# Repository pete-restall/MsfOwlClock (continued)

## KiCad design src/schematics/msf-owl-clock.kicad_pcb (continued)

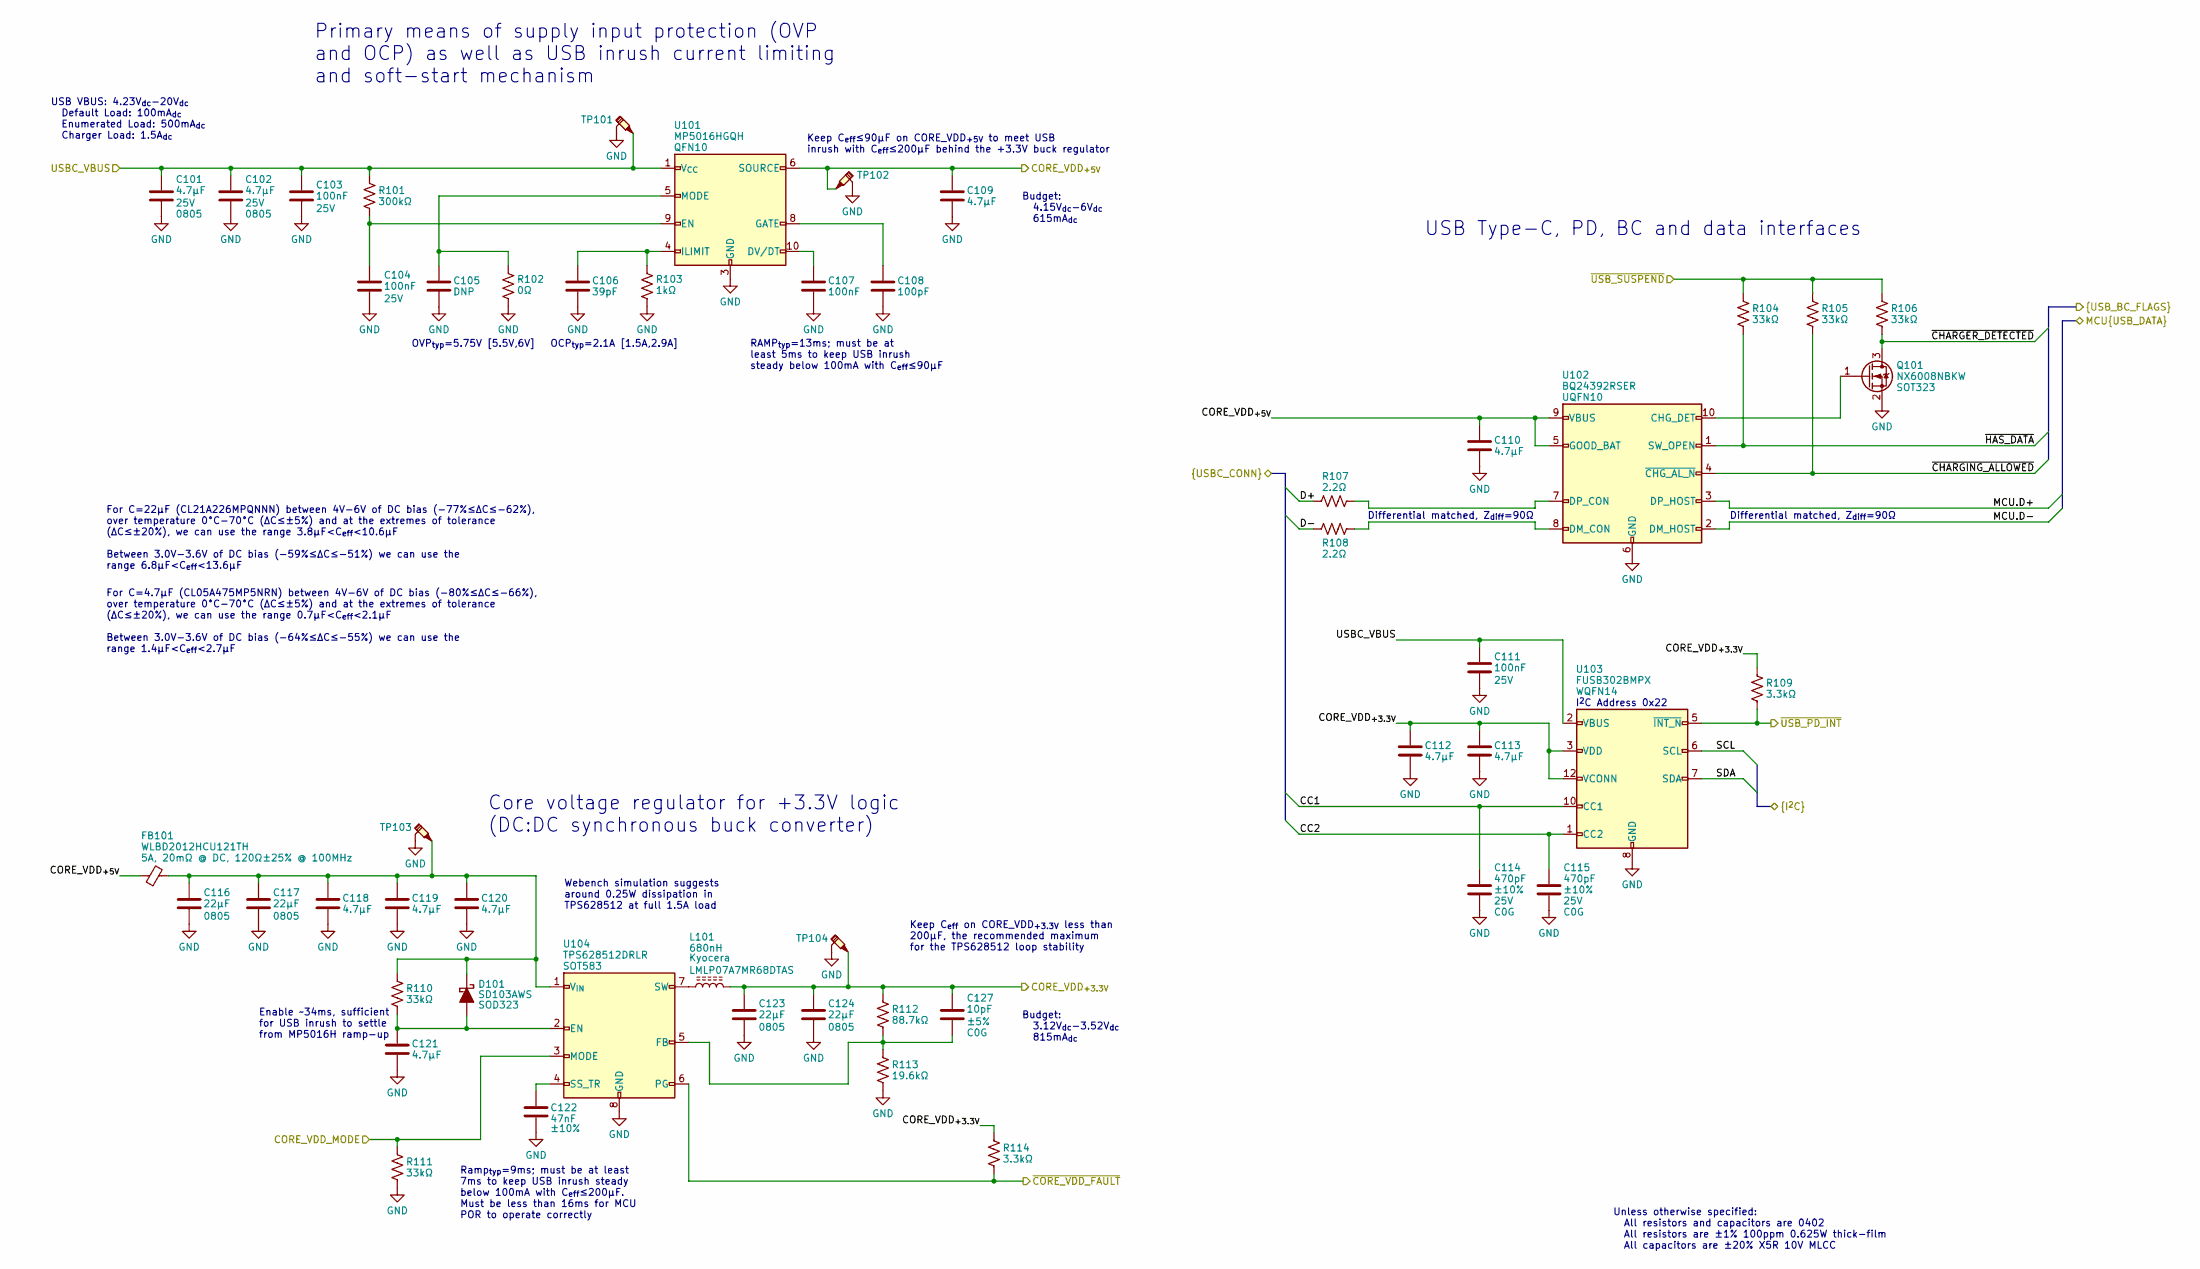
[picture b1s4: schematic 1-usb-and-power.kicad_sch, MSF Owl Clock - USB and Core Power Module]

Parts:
C101, C102: 4.7μF; unpolarised-nominal-0805-2012; Tolerance ±10%; VoltageRating 25V; ManufacturerPartNumber CL21A475KAQNNNE
C103, C104, C111: 100nF; unpolarised-nominal-0402-1005; Tolerance ±20%; VoltageRating 25V; ManufacturerPartNumber CL05B104KA5NNNC
C105: DNP; unpolarised-nominal-0402-1005; Tolerance ±10%; VoltageRating 10V
C106: 39pF; unpolarised-nominal-0402-1005; Tolerance ±10%; VoltageRating 10V; ManufacturerPartNumber CC0402JRNPO9BN390
C107: 100nF; unpolarised-nominal-0402-1005; Tolerance ±20%; VoltageRating 10V; ManufacturerPartNumber CL05B104KA5NNNC
C108: 100pF; unpolarised-nominal-0402-1005; Tolerance ±10%; VoltageRating 10V; ManufacturerPartNumber GMC04CG101G50NT
C109, C110, C112, C113, C118, C119, C120, C121: 4.7μF; unpolarised-nominal-0402-1005; Tolerance ±20%; VoltageRating 10V; ManufacturerPartNumber CL05A475MP5NRNC
C114, C115: 470pF; unpolarised-nominal-0402-1005; Tolerance ±10%; VoltageRating 25V; ManufacturerPartNumber GCM1555C1H471FA16D
C116, C117, C123, C124: 22μF; unpolarised-nominal-0805-2012; Tolerance ±20%; VoltageRating 10V; ManufacturerPartNumber CL21A226MPQNNN
C122: 47nF; unpolarised-nominal-0402-1005; Tolerance ±10%; VoltageRating 10V; ManufacturerPartNumber VJ0402Y473KXQCW1BC
C127: 10pF; unpolarised-nominal-0402-1005; Tolerance ±5%; VoltageRating 10V; ManufacturerPartNumber 885012005007
D101: SD103AWS; SOD323; ManufacturerPartNumber SD103AWS
FB101: WLBD2012HCU121TH; WLBD2012; Tolerance ±25%; ManufacturerPartNumber WLBD2012HCU121TH
L101: 680nH; 07A7; Tolerance ±20%; ManufacturerPartNumber LMLP07A7MR68DTAS
Q101: NX6008NBKW; SOT323; ManufacturerPartNumber NX6008NBKW
R101: 300kΩ; nominal-0402-1005; Tolerance ±1%; ManufacturerPartNumber RC0402FR-07300KL
R102: 0Ω; nominal-0402-1005; Tolerance ±1%; ManufacturerPartNumber RC0402FR-070RL
R103: 1kΩ; nominal-0402-1005; Tolerance ±1%; ManufacturerPartNumber WR04X1001FTL
R104, R105, R106, R110, R111: 33kΩ; nominal-0402-1005; Tolerance ±1%; ManufacturerPartNumber WR04X3302FTL
R107, R108: 2.2Ω; nominal-0402-1005; Tolerance ±1%; ManufacturerPartNumber RMCF0402FT2R20
R109, R114: 3.3kΩ; nominal-0402-1005; Tolerance ±1%; ManufacturerPartNumber CRCW04022R20FKED
R112: 88.7kΩ; nominal-0402-1005; Tolerance ±1%; ManufacturerPartNumber WR04X8872FTL
R113: 19.6kΩ; nominal-0402-1005; Tolerance ±1%; ManufacturerPartNumber WR04X1962FTL
TP101, TP102, TP103, TP104: testpoint-SP3050A-with-short-gnd
U101: MP5016HGQH; QFN10-1.5x2.0mm-0.5mm; ManufacturerPartNumber MP5016HGQH
U102: BQ24392RSER; UQFN10-1.5x2.0mm-0.5mm; ManufacturerPartNumber BQ24392RSER
U103: FUSB302BMPX; WQFN14-2.5x2.5mm-0.5mm-expad-1.45x1.45mm-thermvias; ManufacturerPartNumber FUSB302BMPX
U104: TPS628512DRLR; SOT583; ManufacturerPartNumber TPS628512DRLR

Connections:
/1-usb-and-power/CC1: C114.1, U103.10 (CC1), U103.11 (CC1); also elsewhere on the board
/1-usb-and-power/CC2: C115.1, U103.1 (CC2), U103.14 (CC2); also elsewhere on the board
/1-usb-and-power/CORE_VDD_MODE: R111.1, U104.3 (MODE); also elsewhere on the board
/1-usb-and-power/CORE_VDD_{+5V}: C109.1, C110.1, FB101.1 (P1_PWRIN), TP102.1, U101.6 (SOURCE), U102.5 (GOOD_BAT), U102.9 (VBUS); also elsewhere on the board
/1-usb-and-power/D+: R107.1; also elsewhere on the board
/1-usb-and-power/D-: R108.1; also elsewhere on the board
/1-usb-and-power/MCU.D+: U102.3 (DP_HOST); also elsewhere on the board
/1-usb-and-power/MCU.D-: U102.2 (DM_HOST); also elsewhere on the board
/1-usb-and-power/SCL: U103.6 (SCL); also elsewhere on the board
/1-usb-and-power/SDA: U103.7 (SDA); also elsewhere on the board
/1-usb-and-power/USBC_VBUS: C101.1, C102.1, C103.1, C111.1, R101.1, TP101.1, U101.1 (V_{CC}), U103.2 (VBUS); also elsewhere on the board
/1-usb-and-power/~CHARGER_DETECTED: Q101.3 (D), R106.2; also elsewhere on the board
/1-usb-and-power/~CHARGING_ALLOWED: R105.2, U102.4 (~CHG_AL_N); also elsewhere on the board
/1-usb-and-power/~CORE_VDD_FAULT: R114.2, U104.6 (PG); also elsewhere on the board
/1-usb-and-power/~HAS_DATA: R104.2, U102.1 (SW_OPEN); also elsewhere on the board
/1-usb-and-power/~USB_PD_INT: R109.2, U103.5 (~INT_N); also elsewhere on the board
/1-usb-and-power/~USB_SUSPEND: R104.1, R105.1, R106.1; also elsewhere on the board
/CORE_VDD_{+3.3V}: C112.1, C113.1, C123.1, C124.1, C127.1, L101.2 (P2_PWROUT), R109.1, R112.1, R114.1, TP104.1, U103.3 (VDD), U103.4 (VDD), U103.12 (VCONN), U103.13 (VCONN); also elsewhere on the board
unnamed: C121.1, D101.2 (A), R110.2, U104.2 (EN)
unnamed: C116.1, C117.1, C118.1, C119.1, C120.1, D101.1 (K), FB101.2 (P2_PWROUT), R110.1, TP103.1, U104.1 (V_{IN})
unnamed: L101.1, U104.7 (SW)
unnamed: Q101.1 (G), U102.10 (CHG_DET)
unnamed: C107.1, U101.10 (DV/DT)
unnamed: C104.1, R101.2, U101.9 (EN)
unnamed: C108.1, U101.8 (GATE)
unnamed: C106.1, R103.1, U101.4 (ILIMIT)
unnamed: C105.1, R102.1, U101.5 (MODE)
unnamed: R108.2, U102.8 (DM_CON)
unnamed: R107.2, U102.7 (DP_CON)
unnamed: C127.2, R112.2, R113.1, U104.5 (FB)
unnamed: C122.1, U104.4 (SS_TR)

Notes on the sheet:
Unless otherwise specified: All resistors and capacitors are 0402 All resistors are ±1% 100ppm 0.625W thick-film All capacitors are ±20% X5R 10V MLCC
Ramp_{typ}=9ms; must be at least 7ms to keep USB inrush steady below 100mA with C_{eff}≤200μF. Must be less than 16ms for MCU POR to operate correctly
Webench simulation suggests around 0.25W dissipation in TPS628512 at full 1.5A load
I^{2}C Address 0x22
Keep C_{eff}≤90μF on CORE_VDD_{+5V} to meet USB inrush with C_{eff}≤200μF behind the +3.3V buck regulator
Differential matched, Z_{diff}=90Ω
Enable ~34ms, sufficient for USB inrush to settle from MP5016H ramp-up
Primary means of supply input protection (OVP and OCP) as well as USB inrush current limiting and soft-start mechanism
Budget: 4.15V_{dc}-6V_{dc} 615mA_{dc}
For C=22μF (CL21A226MPQNNN) between 4V-6V of DC bias (-77%≤ΔC≤-62%), over temperature 0°C-70°C (ΔC≤±5%) and at the extremes of tolerance (ΔC≤±20%), we can use the range 3.8μF<C_{eff}<10.6μF Between 3.0V-3.6V of DC bias (-59%≤ΔC≤-51%) we can use the range 6.8μF<C_{eff}<13.6μF
Budget: 3.12V_{dc}-3.52V_{dc} 815mA_{dc}
USB VBUS: 4.23V_{dc}-20V_{dc} Default Load: 100mA_{dc} Enumerated Load: 500mA_{dc} Charger Load: 1.5A_{dc}
RAMP_{typ}=13ms; must be at least 5ms to keep USB inrush steady below 100mA with C_{eff}≤90μF
OCP_{typ}=2.1A [1.5A,2.9A]
Core voltage regulator for +3.3V logic (DC:DC synchronous buck converter)
For C=4.7μF (CL05A475MP5NRN) between 4V-6V of DC bias (-80%≤ΔC≤-66%), over temperature 0°C-70°C (ΔC≤±5%) and at the extremes of tolerance (ΔC≤±20%), we can use the range 0.7μF<C_{eff}<2.1μF Between 3.0V-3.6V of DC bias (-64%≤ΔC≤-55%) we can use the range 1.4μF<C_{eff}<2.7μF
OVP_{typ}=5.75V [5.5V,6V]
Keep C_{eff} on CORE_VDD_{+3.3V} less than 200μF, the recommended maximum for the TPS628512 loop stability
USB Type-C, PD, BC and data interfaces

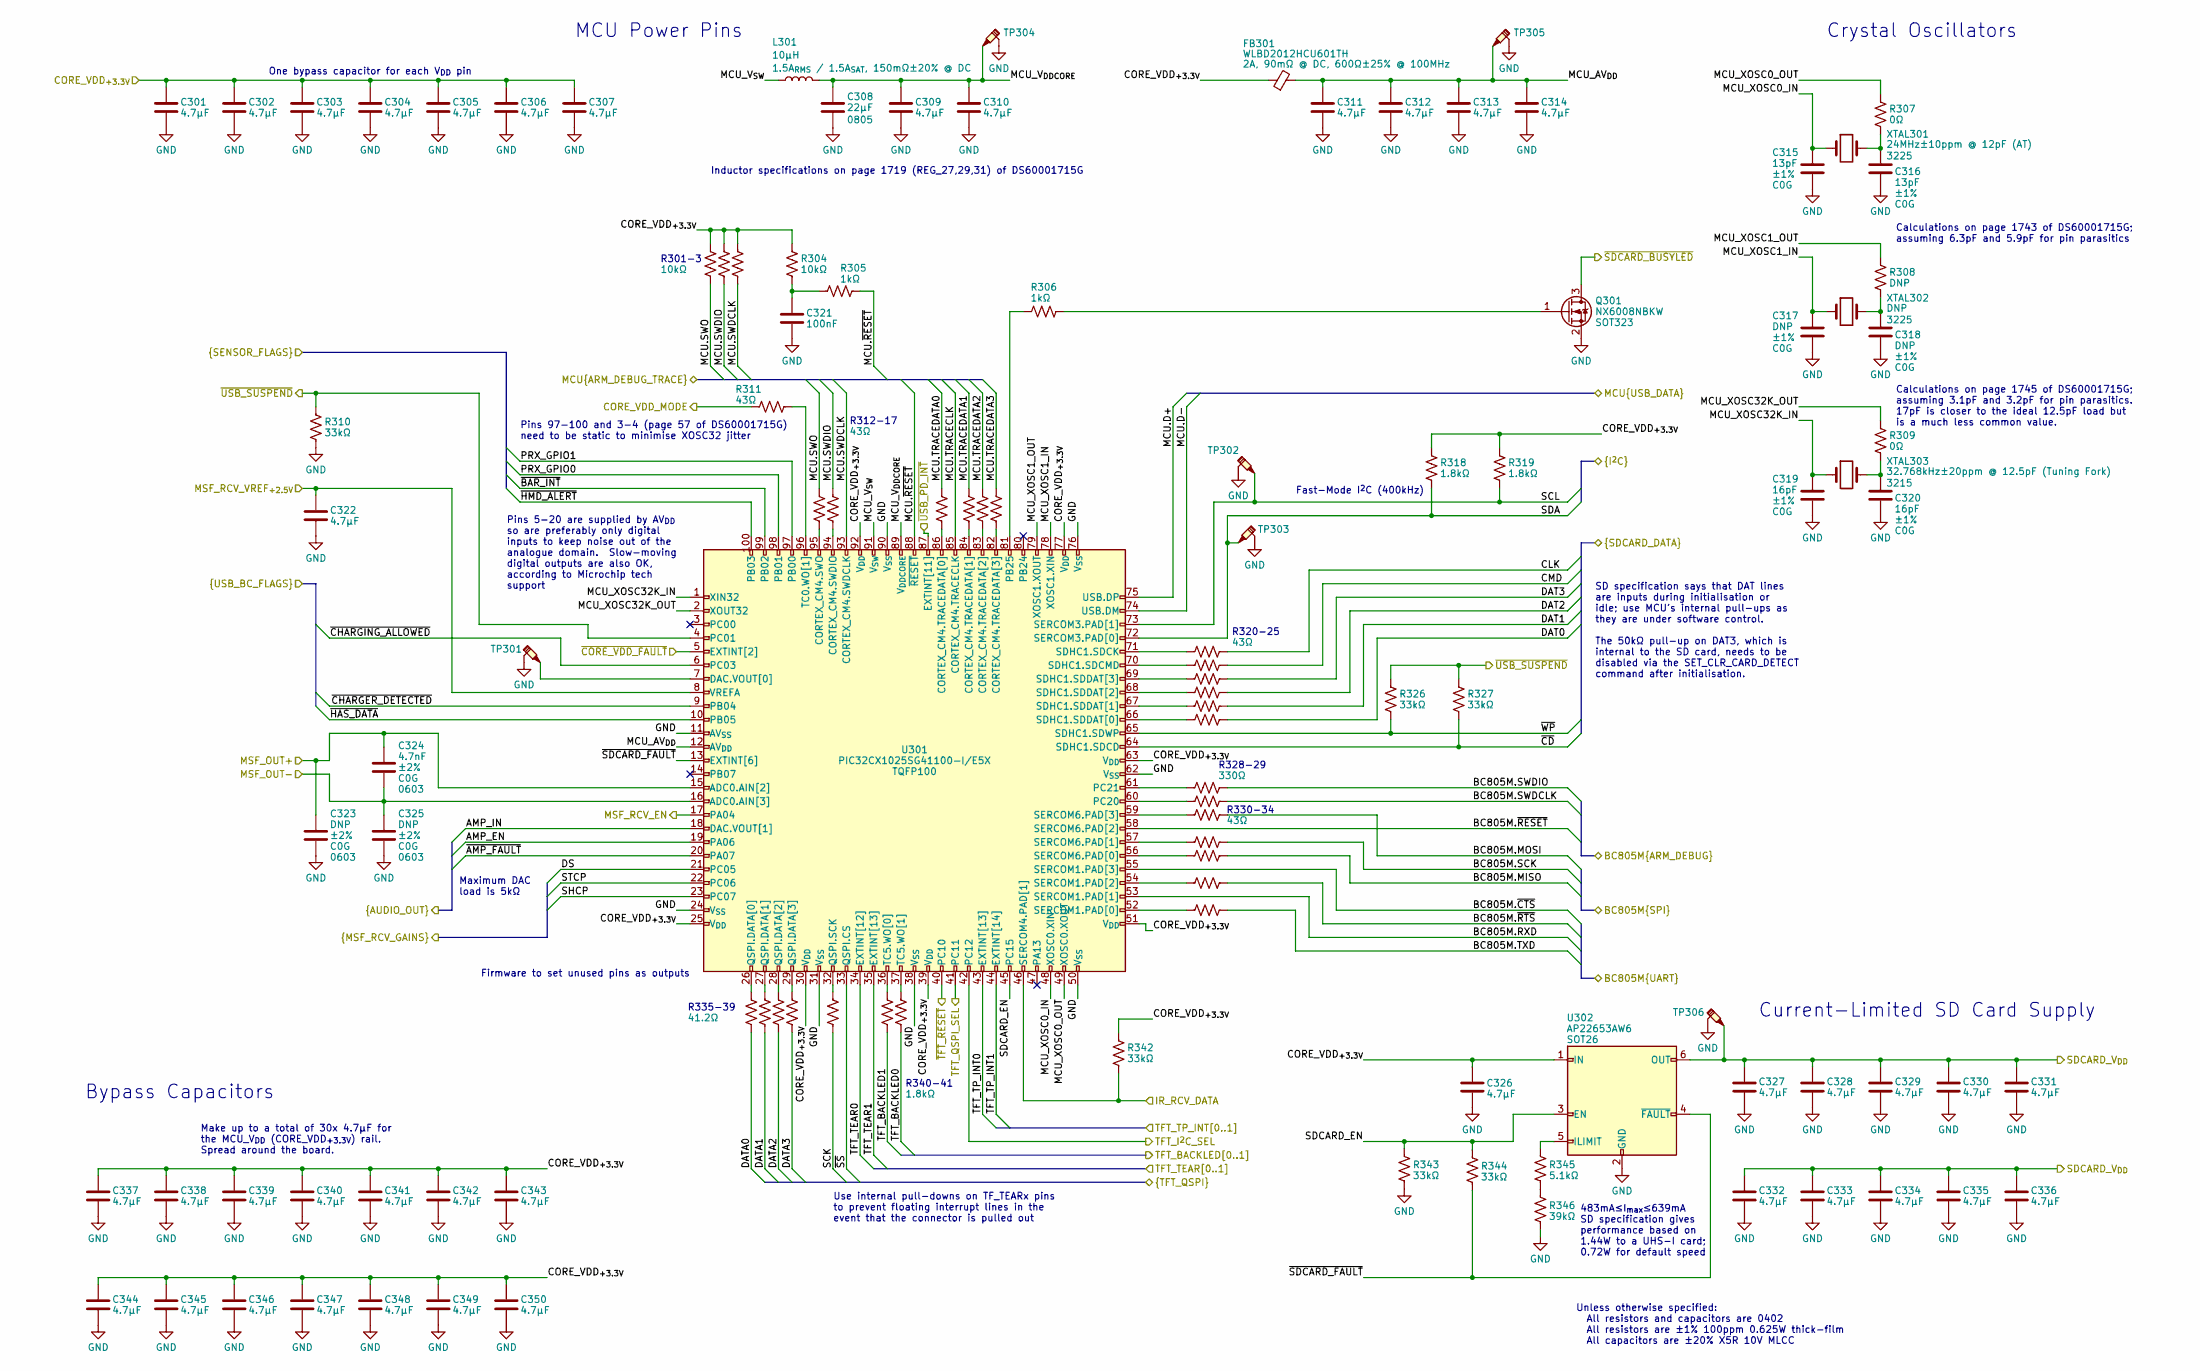
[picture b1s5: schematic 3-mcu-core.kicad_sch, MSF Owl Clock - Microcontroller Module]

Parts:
C301, C302, C303, C304, C305, C306, C307, C309, C310, C311, C312, C313, C314, C322, C326, C327, C328, C329, C330, C331, C332, C333, C334, C335, C336, C337, C338, C339, C340, C341, C342, C343, C344, C345, C346, C347, C348, C349, C350: 4.7μF; unpolarised-nominal-0402-1005; Tolerance ±20%; VoltageRating 10V; ManufacturerPartNumber CL05A475MP5NRNC
C308: 22μF; unpolarised-nominal-0805-2012; Tolerance ±20%; VoltageRating 10V; ManufacturerPartNumber CL21A226MPQNNN
C315, C316: 13pF; unpolarised-nominal-0402-1005; Tolerance ±1%; VoltageRating 10V; ManufacturerPartNumber GJM1555C1H130FB01D
C317, C318: DNP; unpolarised-nominal-0402-1005; Tolerance ±1%; VoltageRating 10V
C319, C320: 16pF; unpolarised-nominal-0402-1005; Tolerance ±1%; VoltageRating 10V; ManufacturerPartNumber GCM1555C1H160FA16D
C321: 100nF; unpolarised-nominal-0402-1005; Tolerance ±20%; VoltageRating 10V; ManufacturerPartNumber CL05B104KA5NNNC
C323, C325: DNP; unpolarised-nominal-0603-1608; Tolerance ±2%; VoltageRating 10V
C324: 4.7nF; unpolarised-nominal-0603-1608; Tolerance ±2%; VoltageRating 10V; ManufacturerPartNumber CC0603FRNPO9BN472
FB301: WLBD2012HCU601TH; WLBD2012; Tolerance ±25%; ManufacturerPartNumber WLBD2012HCU601TH
L301: 10μH; HPC4018NF; Tolerance ±20%; ManufacturerPartNumber HPC4018NF-100M
Q301: NX6008NBKW; SOT323; ManufacturerPartNumber NX6008NBKW
R301, R302, R303, R304: 10kΩ; nominal-0402-1005; Tolerance ±1%; ManufacturerPartNumber WR04X1002FTL
R305, R306: 1kΩ; nominal-0402-1005; Tolerance ±1%; ManufacturerPartNumber WR04X1001FTL
R307, R309: 0Ω; nominal-0402-1005; Tolerance ±1%; ManufacturerPartNumber RC0402FR-070RL
R308: DNP; nominal-0402-1005; Tolerance ±1%
R310, R326, R327, R342, R343, R344: 33kΩ; nominal-0402-1005; Tolerance ±1%; ManufacturerPartNumber WR04X3302FTL
R311, R312, R313, R314, R315, R316, R317, R320, R321, R322, R323, R324, R325, R330, R331, R332, R333, R334: 43Ω; nominal-0402-1005; Tolerance ±1%; ManufacturerPartNumber RC0402FR-0743RL
R318, R319, R340, R341: 1.8kΩ; nominal-0402-1005; Tolerance ±1%; ManufacturerPartNumber RC0402FR-071K8L
R328, R329: 330Ω; nominal-0402-1005; Tolerance ±1%; ManufacturerPartNumber WR04X3300FTL
R335, R336, R337, R338, R339: 41.2Ω; nominal-0402-1005; Tolerance ±1%; ManufacturerPartNumber RC0402FR-0741R2L
R345: 5.1kΩ; nominal-0402-1005; Tolerance ±1%; ManufacturerPartNumber WR04X5101FTL
R346: 39kΩ; nominal-0402-1005; Tolerance ±1%; ManufacturerPartNumber RC0402FR-0739KL
TP301, TP302, TP303, TP304, TP305, TP306: testpoint-SP3050A-with-short-gnd
U301: PIC32CX1025SG41100-I/E5X; TQFP100-14x14mm-0.5mm; ManufacturerPartNumber PIC32CX1025SG41100-I/E5X
U302: AP22653AW6; SOT26; ManufacturerPartNumber AP22653AW6-7
XTAL301: 24MHz; 3225-1-3; Tolerance ±10ppm; ManufacturerPartNumber RH100-24.000-12-1010-EXT-TR
XTAL302: 8-48MHz; 3225-1-3; Tolerance ±10ppm
XTAL303: 32.768kHz; 3215; Tolerance ±20ppm; ManufacturerPartNumber DH2032K768C5T1521011

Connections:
/1-usb-and-power/CORE_VDD_MODE: R311.1; also elsewhere on the board
/1-usb-and-power/MCU.D+: U301.75 (USB.DP); also elsewhere on the board
/1-usb-and-power/MCU.D-: U301.74 (USB.DM); also elsewhere on the board
/1-usb-and-power/SCL: R319.2, TP302.1, U301.73 (SERCOM3.PAD[1]); also elsewhere on the board
/1-usb-and-power/SDA: R318.2, TP303.1, U301.72 (SERCOM3.PAD[0]); also elsewhere on the board
/1-usb-and-power/~CHARGER_DETECTED: U301.9 (PB04); also elsewhere on the board
/1-usb-and-power/~CHARGING_ALLOWED: U301.6 (PC03); also elsewhere on the board
/1-usb-and-power/~CORE_VDD_FAULT: U301.5 (EXTINT[2]); also elsewhere on the board
/1-usb-and-power/~HAS_DATA: U301.10 (PB05); also elsewhere on the board
/1-usb-and-power/~USB_PD_INT: U301.87 (EXTINT[11]); also elsewhere on the board
/1-usb-and-power/~USB_SUSPEND: R310.1, R326.1, R327.1, U301.4 (PC01); also elsewhere on the board
/2-msf-receiver/DS: U301.21 (PC05); also elsewhere on the board
/2-msf-receiver/MSF_OUT+: C323.2, C324.2, U301.15 (ADC0.AIN[2]); also elsewhere on the board
/2-msf-receiver/MSF_OUT-: C324.1, C325.2, U301.16 (ADC0.AIN[3]); also elsewhere on the board
/2-msf-receiver/MSF_RCV_EN: U301.17 (PA04); also elsewhere on the board
/2-msf-receiver/MSF_RCV_VREF_{+2.5V}: C322.1, U301.8 (VREFA); also elsewhere on the board
/2-msf-receiver/SHCP: U301.23 (PC07); also elsewhere on the board
/2-msf-receiver/STCP: U301.22 (PC06); also elsewhere on the board
/3-mcu-core/AMP_EN: U301.19 (PA06); also elsewhere on the board
/3-mcu-core/AMP_IN: U301.18 (DAC.VOUT[1]); also elsewhere on the board
/3-mcu-core/BC805M.MISO: R332.2; also elsewhere on the board
/3-mcu-core/BC805M.MOSI: R330.2; also elsewhere on the board
/3-mcu-core/BC805M.RXD: U301.53 (SERCOM1.PAD[1]); also elsewhere on the board
/3-mcu-core/BC805M.SCK: R331.2; also elsewhere on the board
/3-mcu-core/BC805M.SWDCLK: R329.2; also elsewhere on the board
/3-mcu-core/BC805M.SWDIO: R328.2; also elsewhere on the board
/3-mcu-core/BC805M.TXD: R334.2; also elsewhere on the board
/3-mcu-core/BC805M.~CTS: U301.55 (SERCOM1.PAD[3]); also elsewhere on the board
/3-mcu-core/BC805M.~RESET: U301.58 (SERCOM6.PAD[2]); also elsewhere on the board
/3-mcu-core/BC805M.~RTS: R333.2; also elsewhere on the board
/3-mcu-core/CLK: R320.2; also elsewhere on the board
/3-mcu-core/CMD: R321.2; also elsewhere on the board
/3-mcu-core/DAT0: R325.2; also elsewhere on the board
/3-mcu-core/DAT1: R324.2; also elsewhere on the board
/3-mcu-core/DAT2: R323.2; also elsewhere on the board
/3-mcu-core/DAT3: R322.2; also elsewhere on the board
/3-mcu-core/DATA0: R335.1; also elsewhere on the board
/3-mcu-core/DATA1: R336.1; also elsewhere on the board
/3-mcu-core/DATA2: R337.1; also elsewhere on the board
/3-mcu-core/DATA3: R338.1; also elsewhere on the board
/3-mcu-core/IR_RCV_DATA: R342.2, U301.46 (SERCOM4.PAD[1]); also elsewhere on the board
/3-mcu-core/MCU.SWDCLK: R303.1, U301.93 (CORTEX_CM4.SWDCLK); also elsewhere on the board
/3-mcu-core/MCU.SWDIO: R302.1, R313.2; also elsewhere on the board
/3-mcu-core/MCU.SWO: R301.1, R312.2; also elsewhere on the board
/3-mcu-core/MCU.TRACECLK: U301.85 (CORTEX_CM4.TRACECLK); also elsewhere on the board
/3-mcu-core/MCU.TRACEDATA0: R314.2; also elsewhere on the board
/3-mcu-core/MCU.TRACEDATA1: R315.2; also elsewhere on the board
/3-mcu-core/MCU.TRACEDATA2: R316.2; also elsewhere on the board
/3-mcu-core/MCU.TRACEDATA3: R317.2; also elsewhere on the board
/3-mcu-core/MCU.~RESET: R305.2, U301.88 (~RESET); also elsewhere on the board
/3-mcu-core/MCU_AV_{DD}: C311.1, C312.1, C313.1, C314.1, FB301.2 (P2_PWROUT), TP305.1, U301.12 (AV_{DD})
/3-mcu-core/MCU_V_{DDCORE}: C308.1, C309.1, C310.1, L301.2, TP304.1, U301.89 (V_{DDCORE})
/3-mcu-core/MCU_V_{SW}: L301.1, U301.91 (V_{SW})
/3-mcu-core/MCU_XOSC0_IN: C315.1, U301.48 (XOSC0.XIN), XTAL301.1
/3-mcu-core/MCU_XOSC0_OUT: R307.1, U301.49 (XOSC0.XOUT)
/3-mcu-core/MCU_XOSC1_IN: C317.1, U301.78 (XOSC1.XIN), XTAL302.1
/3-mcu-core/MCU_XOSC1_OUT: R308.1, U301.79 (XOSC1.XOUT)
/3-mcu-core/MCU_XOSC32K_IN: C319.1, U301.1 (XIN32), XTAL303.1
/3-mcu-core/MCU_XOSC32K_OUT: R309.1, U301.2 (XOUT32)
/3-mcu-core/PRX_GPIO0: U301.98 (PB01); also elsewhere on the board
/3-mcu-core/PRX_GPIO1: U301.97 (PB00); also elsewhere on the board
/3-mcu-core/SCK: R339.1; also elsewhere on the board
/3-mcu-core/SDCARD_EN: R343.1, R344.1, U301.45 (PC15), U302.3 (EN)
/3-mcu-core/SDCARD_V_{DD}: C327.1, C328.1, C329.1, C330.1, C331.1, C332.1, C333.1, C334.1, C335.1, C336.1, TP306.1, U302.6 (OUT); also elsewhere on the board
/3-mcu-core/TFT_BACKLED0: R341.1; also elsewhere on the board
/3-mcu-core/TFT_BACKLED1: R340.1; also elsewhere on the board
/3-mcu-core/TFT_I^{2}C_SEL: U301.42 (PC12); also elsewhere on the board
/3-mcu-core/TFT_QSPI_SEL: U301.41 (PC11); also elsewhere on the board
/3-mcu-core/TFT_TEAR0: U301.34 (EXTINT[12]); also elsewhere on the board
/3-mcu-core/TFT_TEAR1: U301.35 (EXTINT[13]); also elsewhere on the board
/3-mcu-core/TFT_TP_INT0: U301.43 (EXTINT[13]); also elsewhere on the board
/3-mcu-core/TFT_TP_INT1: U301.44 (EXTINT[14]); also elsewhere on the board
/3-mcu-core/~AMP_FAULT: U301.20 (PA07); also elsewhere on the board
/3-mcu-core/~BAR_INT: U301.99 (PB02); also elsewhere on the board
/3-mcu-core/~CD: R327.2, U301.64 (SDHC1.SDCD); also elsewhere on the board
/3-mcu-core/~HMD_ALERT: U301.100 (PB03); also elsewhere on the board
/3-mcu-core/~SDCARD_BUSYLED: Q301.3 (D); also elsewhere on the board
/3-mcu-core/~SDCARD_FAULT: R344.2, U301.13 (EXTINT[6]), U302.4 (~FAULT)
/3-mcu-core/~SS: U301.33 (QSPI.CS); also elsewhere on the board
/3-mcu-core/~TFT_RESET: U301.40 (PC10); also elsewhere on the board
/3-mcu-core/~WP: R326.2, U301.65 (SDHC1.SDWP); also elsewhere on the board
/CORE_VDD_{+3.3V}: C301.1, C302.1, C303.1, C304.1, C305.1, C306.1, C307.1, C326.1, C337.1, C338.1, C339.1, C340.1, C341.1, C342.1, C343.1, C344.1, C345.1, C346.1, C347.1, C348.1, C349.1, C350.1, FB301.1 (P1_PWRIN), R301.2, R302.2, R303.2, R304.1, R318.1, R319.1, R342.1, U301.25 (V_{DD}), U301.30 (V_{DD}), U301.39 (V_{DD}), U301.51 (V_{DD}), U301.63 (V_{DD}), U301.77 (V_{DD}), U301.92 (V_{DD}), U302.1 (IN); also elsewhere on the board
unnamed: C316.1, R307.2, XTAL301.3
unnamed: C318.1, R308.2, XTAL302.3
unnamed: C320.1, R309.2, XTAL303.2
unnamed: C321.1, R304.2, R305.1
unnamed: Q301.1 (G), R306.2
unnamed: R345.2, R346.1
unnamed: TP301.1, U301.7 (DAC.VOUT[0])
unnamed: R335.2, U301.26 (QSPI.DATA[0])
unnamed: R336.2, U301.27 (QSPI.DATA[1])
unnamed: R337.2, U301.28 (QSPI.DATA[2])
unnamed: R338.2, U301.29 (QSPI.DATA[3])
unnamed: R334.1, U301.52 (SERCOM1.PAD[0])
unnamed: R333.1, U301.54 (SERCOM1.PAD[2])
unnamed: R321.1, U301.70 (SDHC1.SDCMD)
unnamed: R320.1, U301.71 (SDHC1.SDCK)
unnamed: R313.1, U301.94 (CORTEX_CM4.SWDIO)
unnamed: R339.2, U301.32 (QSPI.SCK)
unnamed: R340.2, U301.36 (TC5.WO[0])
unnamed: R341.2, U301.37 (TC5.WO[1])
unnamed: R325.1, U301.66 (SDHC1.SDDAT[0])
unnamed: R324.1, U301.67 (SDHC1.SDDAT[1])
unnamed: R323.1, U301.68 (SDHC1.SDDAT[2])
unnamed: R322.1, U301.69 (SDHC1.SDDAT[3])
unnamed: R306.1, U301.81 (PB25)
unnamed: R312.1, U301.95 (CORTEX_CM4.SWO)
unnamed: R311.2, U301.96 (TC0.WO[1])
unnamed: R332.1, U301.56 (SERCOM6.PAD[0])
unnamed: R331.1, U301.57 (SERCOM6.PAD[1])
unnamed: R330.1, U301.59 (SERCOM6.PAD[3])
unnamed: R329.1, U301.60 (PC20)
unnamed: R328.1, U301.61 (PC21)
unnamed: R317.1, U301.82 (CORTEX_CM4.TRACEDATA[3])
unnamed: R316.1, U301.83 (CORTEX_CM4.TRACEDATA[2])
unnamed: R315.1, U301.84 (CORTEX_CM4.TRACEDATA[1])
unnamed: R314.1, U301.86 (CORTEX_CM4.TRACEDATA[0])
unnamed: R345.1, U302.5 (ILIMIT)

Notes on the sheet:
Fast-Mode I^{2}C (400kHz)
Current-Limited SD Card Supply
Use internal pull-downs on TF_TEARx pins to prevent floating interrupt lines in the event that the connector is pulled out
One bypass capacitor for each V_{DD} pin
Maximum DAC load is 5kΩ
R335-39
SD specification says that DAT lines are inputs during initialisation or idle; use MCU's internal pull-ups as they are under software control. The 50kΩ pull-up on DAT3, which is internal to the SD card, needs to be disabled via the SET_CLR_CARD_DETECT command after initialisation.
MCU Power Pins
Pins 5-20 are supplied by AV_{DD} so are preferably only digital inputs to keep noise out of the analogue domain. Slow-moving digital outputs are also OK, according to Microchip tech support
Pins 97-100 and 3-4 (page 57 of DS60001715G) need to be static to minimise XOSC32 jitter
Firmware to set unused pins as outputs
R330-34
R312-17
Calculations on page 1743 of DS60001715G; assuming 6.3pF and 5.9pF for pin parasitics
Make up to a total of 30x 4.7μF for the MCU_V_{DD} (CORE_VDD_{+3.3V}) rail. Spread around the board.
Unless otherwise specified: All resistors and capacitors are 0402 All resistors are ±1% 100ppm 0.625W thick-film All capacitors are ±20% X5R 10V MLCC
R340-41
Bypass Capacitors
R328-29
Calculations on page 1745 of DS60001715G; assuming 3.1pF and 3.2pF for pin parasitics. 17pF is closer to the ideal 12.5pF load but is a much less common value.
R320-25
Inductor specifications on page 1719 (REG_27,29,31) of DS60001715G
R301-3
Crystal Oscillators
483mA≤I_{max}≤639mA SD specification gives performance based on 1.44W to a UHS-I card; 0.72W for default speed

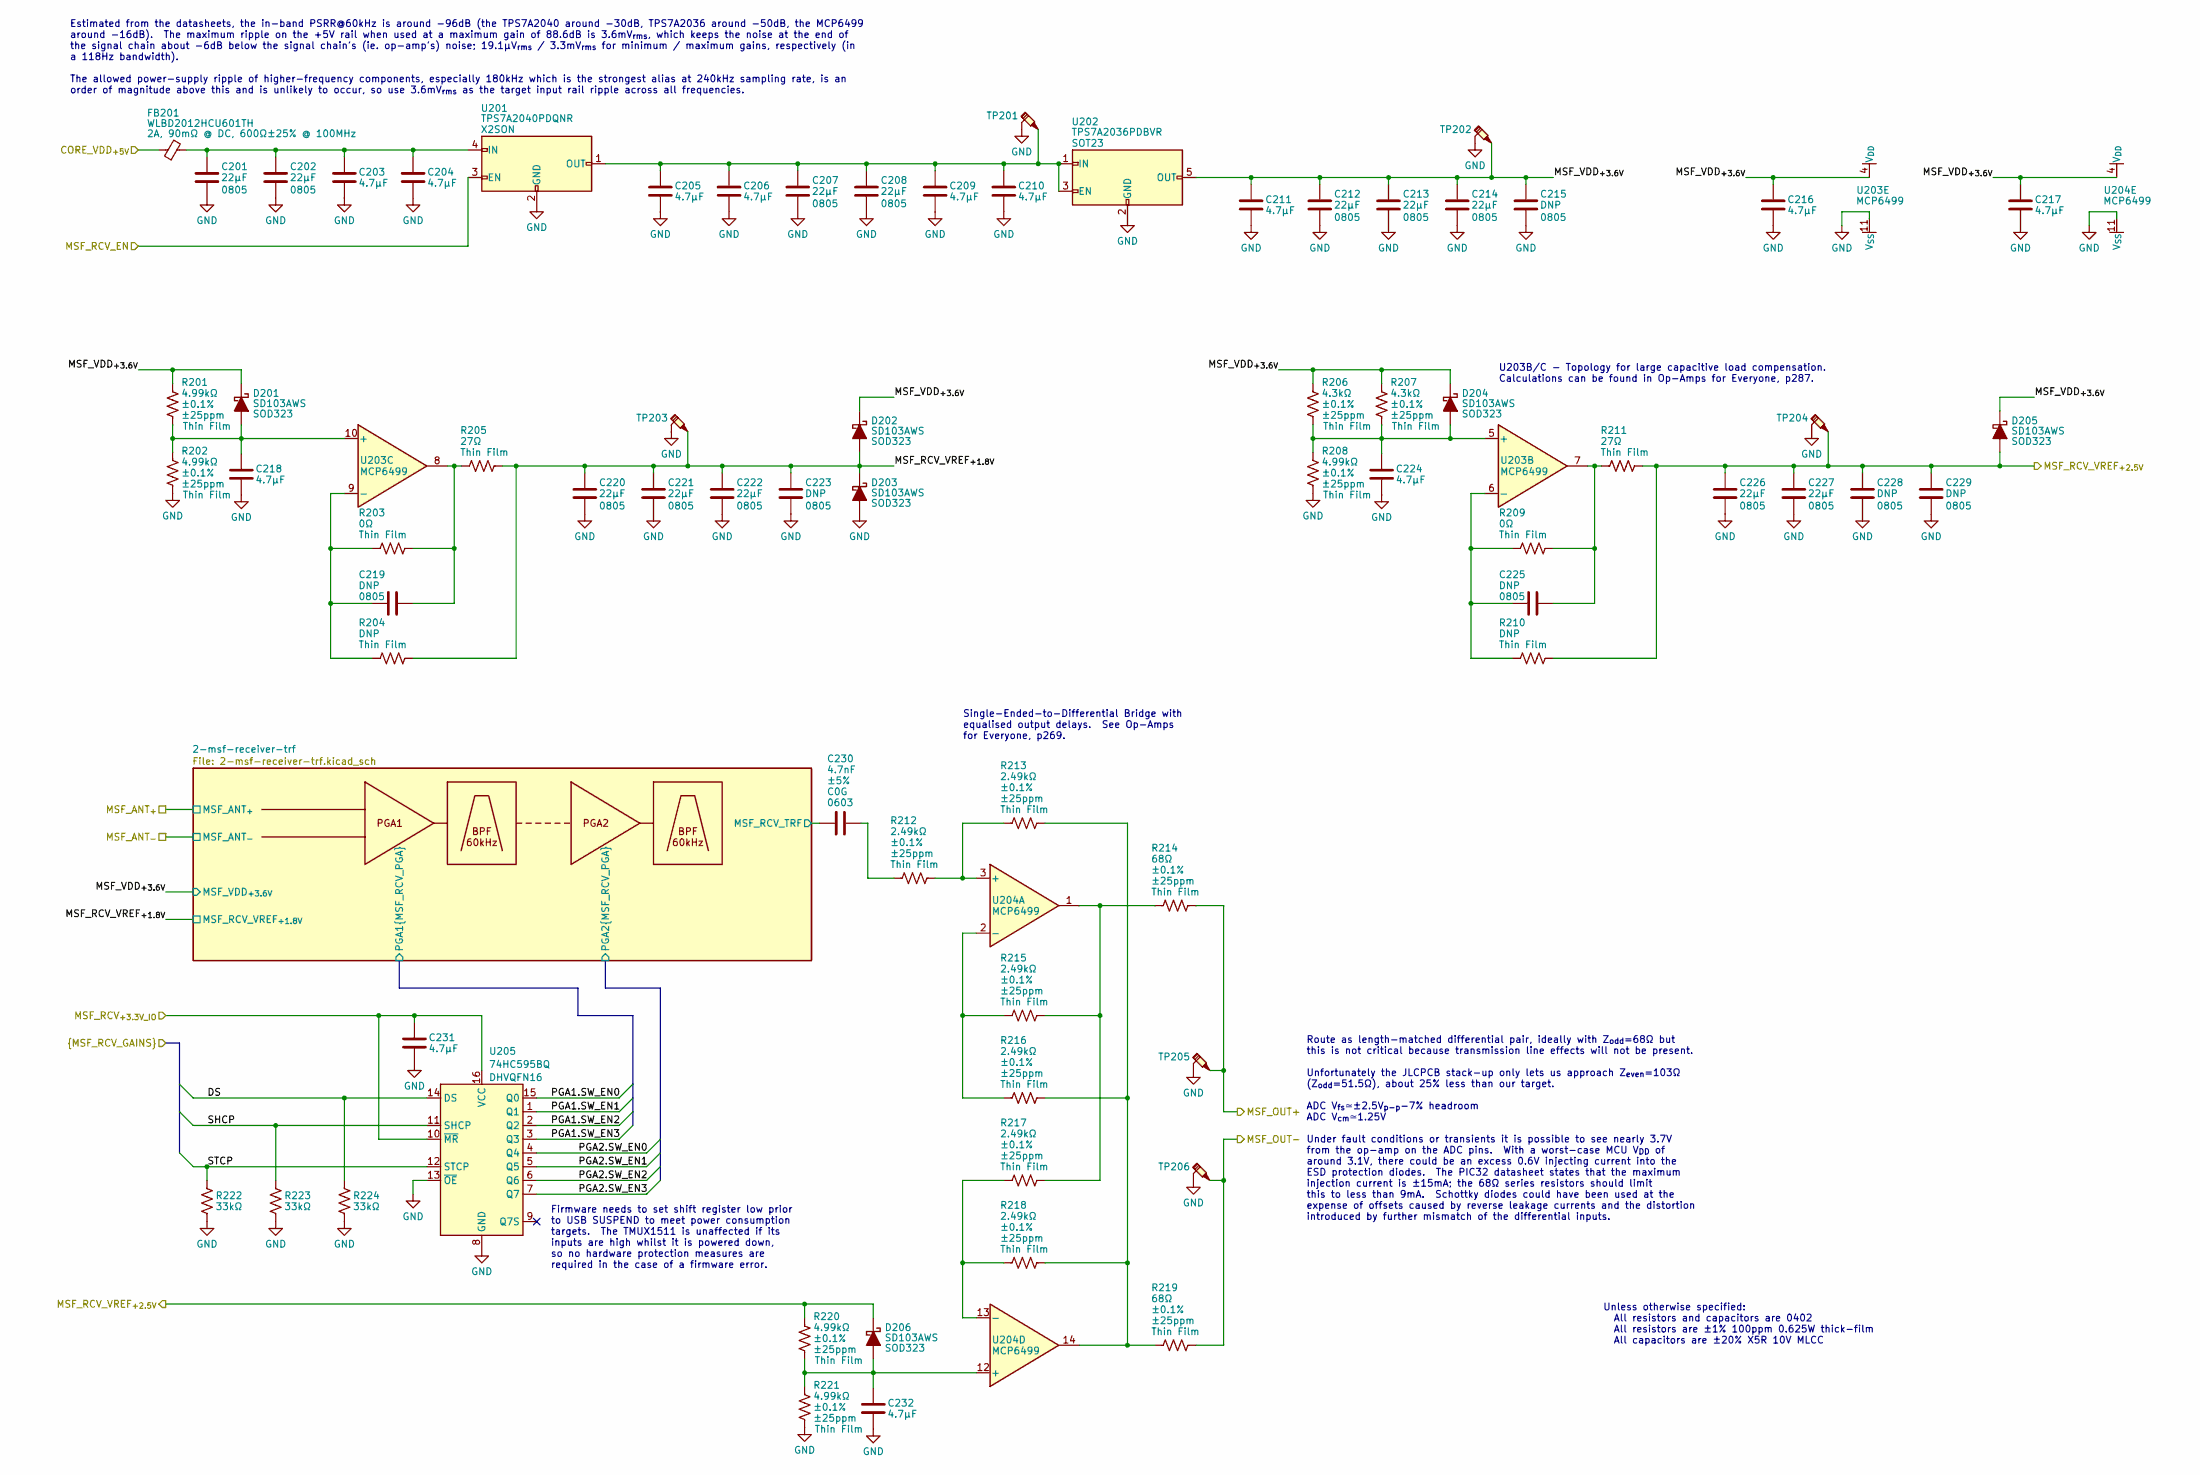
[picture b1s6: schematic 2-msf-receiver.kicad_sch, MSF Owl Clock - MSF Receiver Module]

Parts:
C201, C202, C207, C208, C212, C213, C214, C220, C221, C222, C226, C227: 22μF; unpolarised-nominal-0805-2012; Tolerance ±20%; VoltageRating 10V; ManufacturerPartNumber CL21A226MPQNNN
C203, C204, C205, C206, C209, C210, C211, C216, C217, C218, C224, C231, C232: 4.7μF; unpolarised-nominal-0402-1005; Tolerance ±20%; VoltageRating 10V; ManufacturerPartNumber CL05A475MP5NRNC
C215, C223, C228, C229: DNP; unpolarised-nominal-0805-2012; Tolerance ±20%; VoltageRating 10V; ManufacturerPartNumber CL21A226MPQNNN
C219, C225: DNP; unpolarised-nominal-0805-2012; Tolerance ±20%; VoltageRating 10V
C230: 4.7nF; unpolarised-nominal-0603-1608; Tolerance ±5%; VoltageRating 10V; ManufacturerPartNumber CC0603FRNPO9BN472
D201, D202, D203, D204, D205, D206: SD103AWS; SOD323; ManufacturerPartNumber SD103AWS
FB201: WLBD2012HCU601TH; WLBD2012; Tolerance ±25%; ManufacturerPartNumber WLBD2012HCU601TH
R201, R202, R208, R220, R221: 4.99kΩ; nominal-0402-1005; Tolerance ±0.1%; ManufacturerPartNumber RT0402BRD074K99L
R203, R209: 0Ω; nominal-0402-1005; Tolerance ±1%; ManufacturerPartNumber RC0402FR-070RL
R204, R210: DNP; nominal-0402-1005; Tolerance ±1%
R205, R211: 27Ω; nominal-0402-1005; Tolerance ±1%; ManufacturerPartNumber CPF0402B27RE1
R206, R207: 4.3kΩ; nominal-0402-1005; Tolerance ±0.1%; ManufacturerPartNumber RT0402BRD074K3L
R212, R213, R215, R216, R217, R218: 2.49kΩ; nominal-0402-1005; Tolerance ±0.1%; ManufacturerPartNumber RT0402BRD072K49L
R214, R219: 68Ω; nominal-0402-1005; Tolerance ±0.1%; ManufacturerPartNumber RT0402BRD0768RL
R222, R223, R224: 33kΩ; nominal-0402-1005; Tolerance ±1%; ManufacturerPartNumber WR04X3302FTL
SHEET201: (no value)
TP201, TP202, TP203, TP204, TP205, TP206: testpoint-SP3050A-with-short-gnd
U201: TPS7A2040PDQNR; X2SON4-1x1mm-0.65mm-expad-0.48x0.48mm; ManufacturerPartNumber TPS7A2040PDQNR
U202: TPS7A2036PDBVR; TPS7A20??PDBVR; ManufacturerPartNumber TPS7A2036PDBVR
U203, U204: MCP6499; SOIC14-3.9x8.65mm-1.27mm; ManufacturerPartNumber MCP6499T-E-SL
U205: 74HC595BQ; DHVQFN16-2.5x3.5mm-0.5mm-expad-2x1mm; ManufacturerPartNumber 74HC595BQ

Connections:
/1-usb-and-power/CORE_VDD_{+5V}: FB201.1 (P1_PWRIN); also elsewhere on the board
/2-msf-receiver/2-msf-receiver-trf/MSF_RCV_TRF: C230.2; also elsewhere on the board
/2-msf-receiver/2-msf-receiver-trf/PGA1.SW_EN0: U205.15 (Q0); also elsewhere on the board
/2-msf-receiver/2-msf-receiver-trf/PGA1.SW_EN1: U205.1 (Q1); also elsewhere on the board
/2-msf-receiver/2-msf-receiver-trf/PGA1.SW_EN2: U205.2 (Q2); also elsewhere on the board
/2-msf-receiver/2-msf-receiver-trf/PGA1.SW_EN3: U205.3 (Q3); also elsewhere on the board
/2-msf-receiver/2-msf-receiver-trf/PGA2.SW_EN0: U205.4 (Q4); also elsewhere on the board
/2-msf-receiver/2-msf-receiver-trf/PGA2.SW_EN1: U205.5 (Q5); also elsewhere on the board
/2-msf-receiver/2-msf-receiver-trf/PGA2.SW_EN2: U205.6 (Q6); also elsewhere on the board
/2-msf-receiver/2-msf-receiver-trf/PGA2.SW_EN3: U205.7 (Q7); also elsewhere on the board
/2-msf-receiver/DS: R224.1, U205.14 (DS); also elsewhere on the board
/2-msf-receiver/MSF_OUT+: R214.2, TP205.1; also elsewhere on the board
/2-msf-receiver/MSF_OUT-: R219.2, TP206.1; also elsewhere on the board
/2-msf-receiver/MSF_RCV_EN: U201.3 (EN); also elsewhere on the board
/2-msf-receiver/MSF_RCV_VREF_{+1.8V}: C220.1, C221.1, C222.1, C223.1, D202.2 (A), D203.1 (K), R204.2, R205.2, TP203.1; also elsewhere on the board
/2-msf-receiver/MSF_RCV_VREF_{+2.5V}: C226.1, C227.1, C228.1, C229.1, D205.2 (A), D206.1 (K), R210.2, R211.2, R220.1, TP204.1; also elsewhere on the board
/2-msf-receiver/MSF_VDD_{+3.6V}: C211.1, C212.1, C213.1, C214.1, C215.1, C216.1, C217.1, D201.1 (K), D202.1 (K), D204.1 (K), D205.1 (K), R201.1, R206.1, R207.1, TP202.1, U202.5 (OUT), U203.4 (V_{DD}), U204.4 (V_{DD}); also elsewhere on the board
/2-msf-receiver/SHCP: R223.1, U205.11 (SHCP); also elsewhere on the board
/2-msf-receiver/STCP: R222.1, U205.12 (STCP); also elsewhere on the board
/CORE_VDD_{+3.3V}: C231.1, U205.10 (~MR), U205.16 (VCC); also elsewhere on the board
unnamed: C219.2, R203.2, R205.1, U203.8
unnamed: C225.2, R209.2, R211.1, U203.7
unnamed: C230.1, R212.1
unnamed: C218.1, D201.2 (A), R201.2, R202.1, U203.10 (+)
unnamed: C224.1, D204.2 (A), R206.2, R207.2, R208.1, U203.5 (+)
unnamed: C232.1, D206.2 (A), R220.2, R221.1, U204.12 (+)
unnamed: C201.1, C202.1, C203.1, C204.1, FB201.2 (P2_PWROUT), U201.4 (IN)
unnamed: R213.2, R216.2, R218.2, R219.1, U204.14
unnamed: R214.1, R215.2, R217.2, U204.1
unnamed: C205.1, C206.1, C207.1, C208.1, C209.1, C210.1, TP201.1, U201.1 (OUT), U202.1 (IN), U202.3 (EN)
unnamed: C225.1, R209.1, R210.1, U203.6 (-)
unnamed: C219.1, R203.1, R204.1, U203.9 (-)
unnamed: R212.2, R213.1, U204.3 (+)
unnamed: R215.1, R216.1, U204.2 (-)
unnamed: R217.1, R218.1, U204.13 (-)

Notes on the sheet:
Estimated from the datasheets, the in-band PSRR@60kHz is around -96dB (the TPS7A2040 around -30dB, TPS7A2036 around -50dB, the MCP6499 around -16dB). The maximum ripple on the +5V rail when used at a maximum gain of 88.6dB is 3.6mV_{rms}, which keeps the noise at the end of the signal chain about -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
U203B/C - Topology for large capacitive load compensation. Calculations can be found in Op-Amps for Everyone, p287.
Route as length-matched differential pair, ideally with Z_{odd}=68Ω but this is not critical because transmission line effects will not be present. Unfortunately the JLCPCB stack-up only lets us approach Z_{even}=103Ω (Z_{odd}=51.5Ω), about 25% less than our target. ADC V_{fs}≃±2.5V_{p-p}-7% headro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
Unless otherwise specified: All resistors and capacitors are 0402 All resistors are ±1% 100ppm 0.625W thick-film All capacitors are ±20% X5R 10V MLCC
Firmware needs to set shift register low prior to USB SUSPEND to meet power consumption targets. The TMUX1511 is unaffected if its inputs are high whilst it is powered down, so no hardware protection measures are required in the case of a firmware error.
Single-Ended-to-Differential Bridge with equalised output delays. See Op-Amps for Everyone, p269.
